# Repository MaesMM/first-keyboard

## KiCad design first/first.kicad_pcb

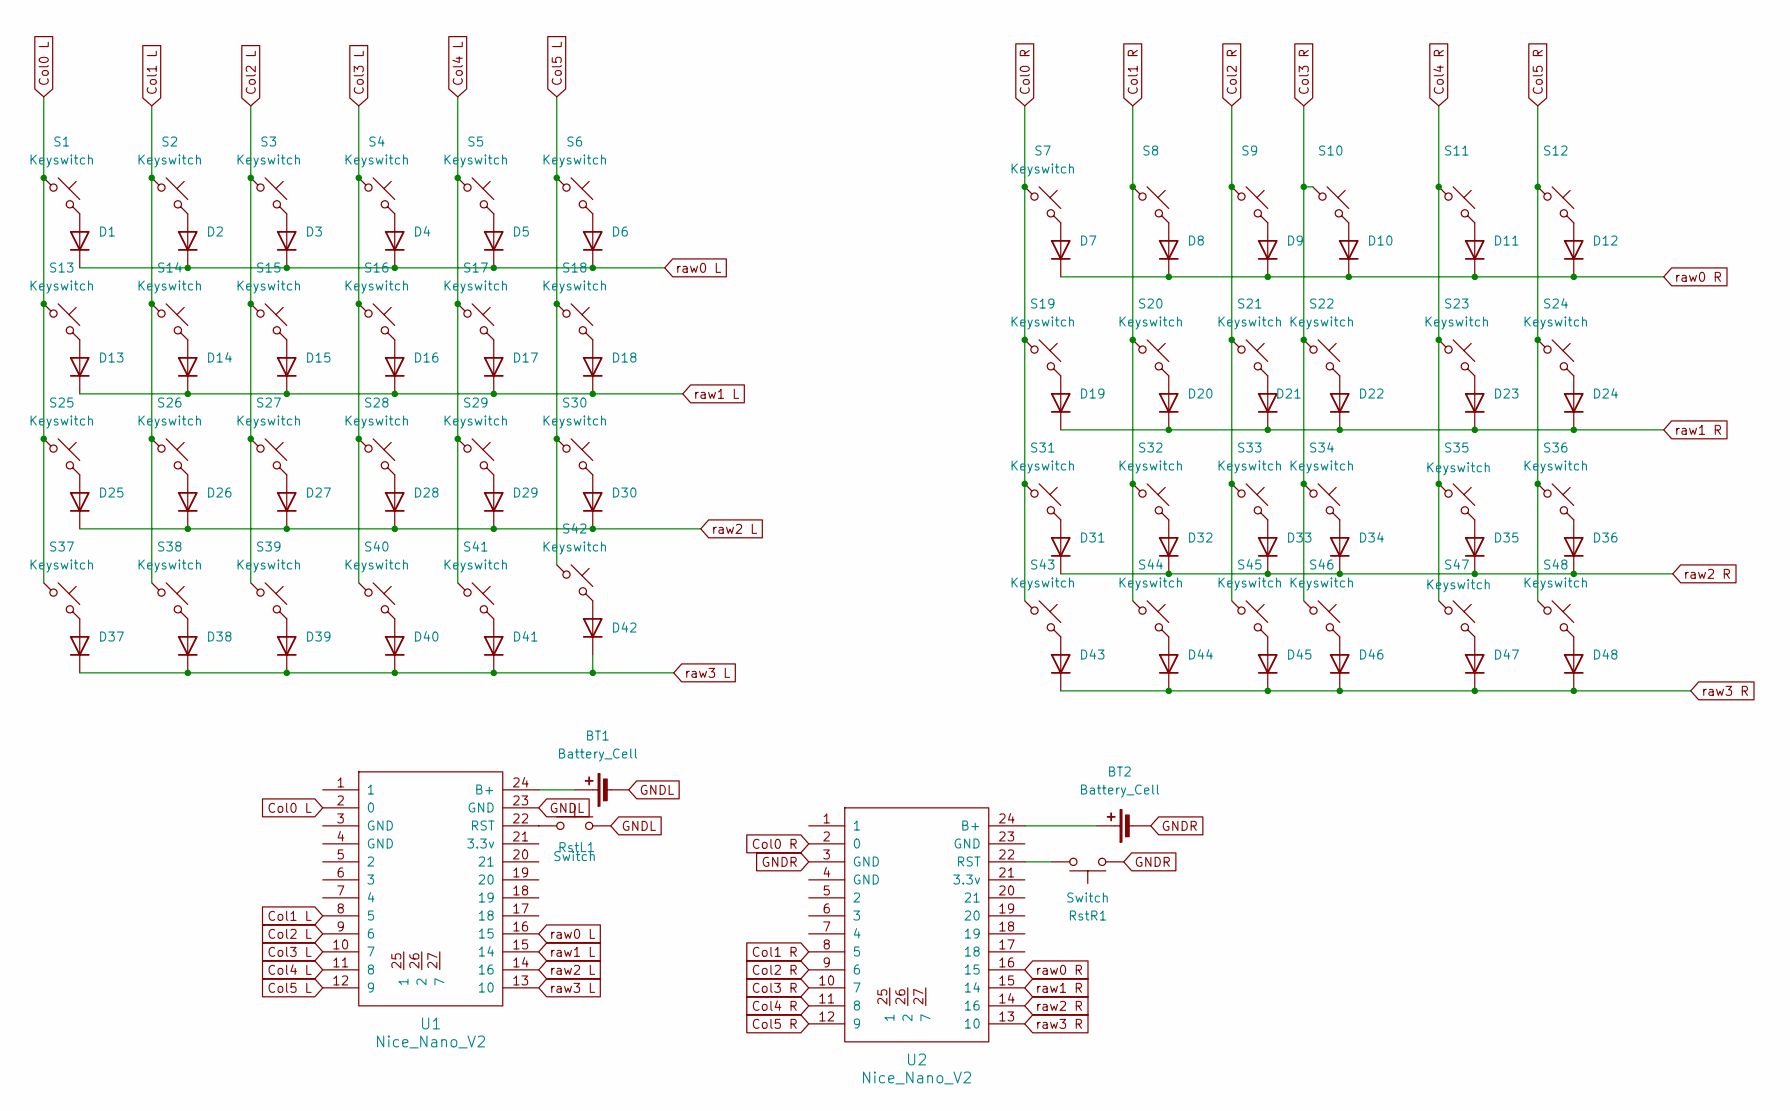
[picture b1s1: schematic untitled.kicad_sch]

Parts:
BT1, BT2: Battery_Cell; Battery
D1, D2, D3, D4, D5, D6, D7, D8, D9, D10, D11, D12, D13, D14, D15, D16, D17, D18, D19, D20, D21, D22, D23, D24, D25, D26, D27, D28, D29, D30, D31, D32, D33, D34, D35, D36, D37, D38, D39, D40, D41, D42, D43, D44, D45, D46, D47, D48: Diode; Diode_DO-35
RstL1: Switch; SW_Slide_SPDT_Straight_CK_OS102011MS2Q
RstR1: Switch; SW_Slide_SPDT_Straight_CK_OS102011MS2Q
S1, S2, S3, S4, S5, S6, S7, S8, S9, S10, S11, S12, S13, S14, S15, S16, S17, S18, S19, S20, S21, S22, S23, S24, S25, S26, S27, S28, S29, S30, S31, S32, S33, S34, S35, S36, S37, S38, S39, S40, S41, S42, S43, S44, S45, S46, S47, S48: Keyswitch; SW_Gateron_LowProfile_HotSwap_THT
U1, U2: Nice_Nano_V2

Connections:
Col0 L: S1.1, S13.1, S25.1, S37.1, U1.2 (0)
Col0 R: S7.1, S19.1, S31.1, S43.1, U2.2 (0)
Col1 L: S2.1, S14.1, S26.1, S38.1, U1.8 (5)
Col1 R: S8.1, S20.1, S32.1, S44.1, U2.8 (5)
Col2 L: S3.1, S15.1, S27.1, S39.1, U1.9 (6)
Col2 R: S9.1, S21.1, S33.1, S45.1, U2.9 (6)
Col3 L: S4.1, S16.1, S28.1, S40.1, U1.10 (7)
Col3 R: S10.1, S22.1, S34.1, S46.1, U2.10 (7)
Col4 L: S5.1, S17.1, S29.1, S41.1, U1.11 (8)
Col4 R: S11.1, S23.1, S35.1, S47.1, U2.11 (8)
Col5 L: S6.1, S18.1, S30.1, S42.1, U1.12 (9)
Col5 R: S12.1, S24.1, S36.1, S48.1, U2.12 (9)
GNDL: BT1.2 (-), RstL1.2, U1.23 (GND)
GNDR: BT2.2 (-), RstR1.1, U2.3 (GND)
unnamed: BT1.1 (+), U1.24 (B+)
unnamed: BT2.1 (+), U2.24 (B+)
unnamed: D1.2 (A), S1.2
unnamed: D2.2 (A), S2.2
unnamed: D3.2 (A), S3.2
unnamed: D4.2 (A), S4.2
unnamed: D5.2 (A), S5.2
unnamed: D6.2 (A), S6.2
unnamed: D7.2 (A), S7.2
unnamed: D8.2 (A), S8.2
unnamed: D9.2 (A), S9.2
unnamed: D10.2 (A), S10.2
unnamed: D11.2 (A), S11.2
unnamed: D12.2 (A), S12.2
unnamed: D13.2 (A), S13.2
unnamed: D14.2 (A), S14.2
unnamed: D15.2 (A), S15.2
unnamed: D16.2 (A), S16.2
unnamed: D17.2 (A), S17.2
unnamed: D18.2 (A), S18.2
unnamed: D19.2 (A), S19.2
unnamed: D20.2 (A), S20.2
unnamed: D21.2 (A), S21.2
unnamed: D22.2 (A), S22.2
unnamed: D23.2 (A), S23.2
unnamed: D24.2 (A), S24.2
unnamed: D25.2 (A), S25.2
unnamed: D26.2 (A), S26.2
unnamed: D27.2 (A), S27.2
unnamed: D28.2 (A), S28.2
unnamed: D29.2 (A), S29.2
unnamed: D30.2 (A), S30.2
unnamed: D31.2 (A), S31.2
unnamed: D32.2 (A), S32.2
unnamed: D33.2 (A), S33.2
unnamed: D34.2 (A), S34.2
unnamed: D35.2 (A), S35.2
unnamed: D36.2 (A), S36.2
unnamed: D37.2 (A), S37.2
unnamed: D38.2 (A), S38.2
unnamed: D39.2 (A), S39.2
unnamed: D40.2 (A), S40.2
unnamed: D41.2 (A), S41.2
unnamed: D42.2 (A), S42.2
unnamed: D43.2 (A), S43.2
unnamed: D44.2 (A), S44.2
unnamed: D45.2 (A), S45.2
unnamed: D46.2 (A), S46.2
unnamed: D47.2 (A), S47.2
unnamed: D48.2 (A), S48.2
unnamed: RstL1.1, U1.22 (RST)
unnamed: RstR1.2, U2.22 (RST)
raw0 L: D1.1 (K), D2.1 (K), D3.1 (K), D4.1 (K), D5.1 (K), D6.1 (K), U1.16 (15)
raw0 R: D7.1 (K), D8.1 (K), D9.1 (K), D10.1 (K), D11.1 (K), D12.1 (K), U2.16 (15)
raw1 L: D13.1 (K), D14.1 (K), D15.1 (K), D16.1 (K), D17.1 (K), D18.1 (K), U1.15 (14)
raw1 R: D19.1 (K), D20.1 (K), D21.1 (K), D22.1 (K), D23.1 (K), D24.1 (K), U2.15 (14)
raw2 L: D25.1 (K), D26.1 (K), D27.1 (K), D28.1 (K), D29.1 (K), D30.1 (K), U1.14 (16)
raw2 R: D31.1 (K), D32.1 (K), D33.1 (K), D34.1 (K), D35.1 (K), D36.1 (K), U2.14 (16)
raw3 L: D37.1 (K), D38.1 (K), D39.1 (K), D40.1 (K), D41.1 (K), D42.1 (K), U1.13 (10)
raw3 R: D43.1 (K), D44.1 (K), D45.1 (K), D46.1 (K), D47.1 (K), D48.1 (K), U2.13 (10)

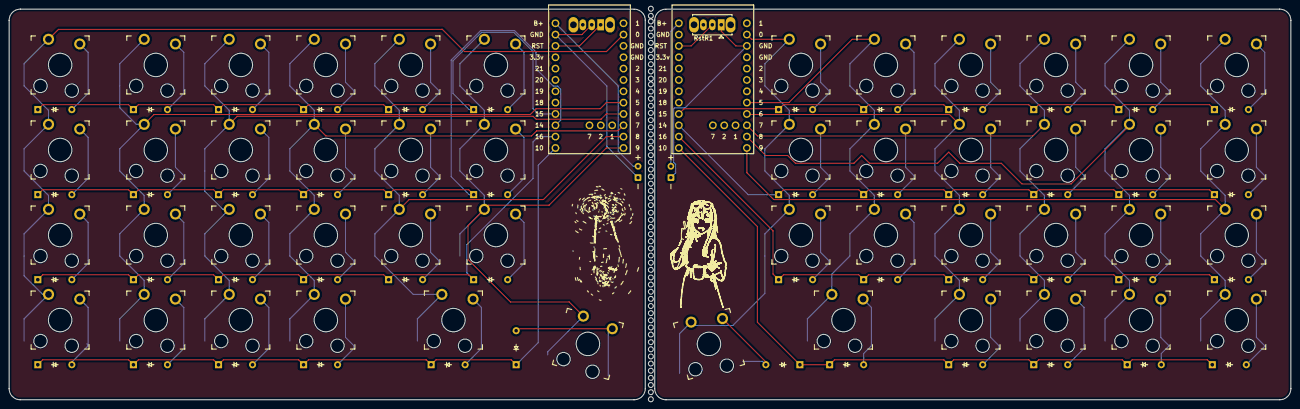
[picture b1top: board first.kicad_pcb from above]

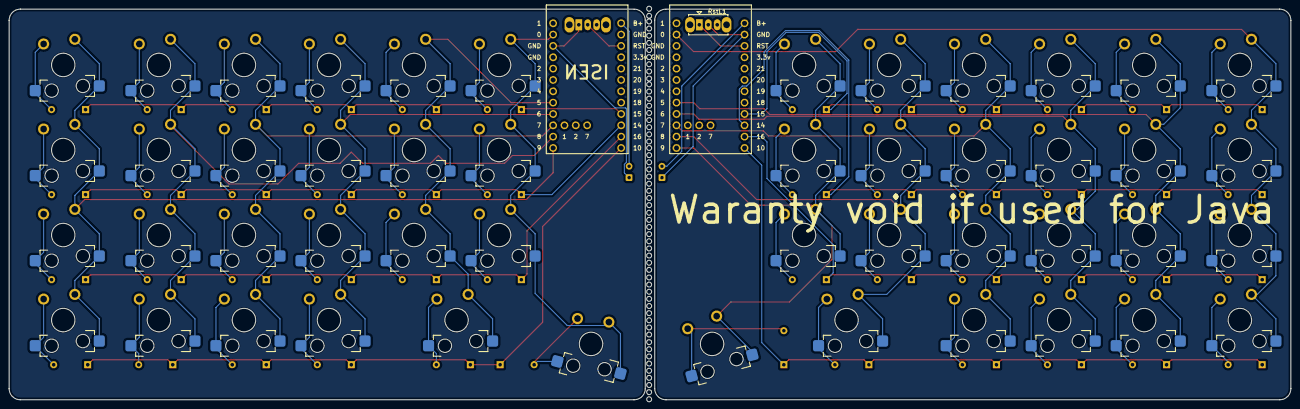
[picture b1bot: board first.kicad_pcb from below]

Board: 2 copper layers, 287.1 x 87.5 mm, 102 parts (3 on the bottom side), 74 nets.

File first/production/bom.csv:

Designator,Footprint,Quantity,Value,LCSC Part #
"_2, ",,2,,
"BT1, BT2",Battery,2,Battery_Cell,
"D1, D10, D11, D12, D13, D14, D15, D16, D17, D18, D19, D2, D20, D21, D22, D23, D24, D25, D26, D27, D28, D29, D3, D30, D31, D32, D33, D34, D35, D36, D37, D38, D39, D4, D40, D41, D42, D43, D44, D45, D46, D47, D48, D5, D6, D7, D8, D9",Diode_DO-35,48,Diode,
"RSTL1, RSTR1",SW_Slide_SPDT_Straight_CK_OS102011MS2Q,2,Switch,
"S1, S10, S11, S12, S13, S14, S15, S16, S17, S18, S19, S2, S20, S21, S22, S23, S24, S25, S26, S27, S28, S29, S3, S30, S31, S32, S33, S34, S35, S36, S37, S38, S39, S4, S40, S41, S42, S43, S44, S45, S46, S47, S48, S5, S6, S7, S8, S9",SW_Gateron_LowProfile_HotSwap_THT,48,Keyswitch,
"U1, U2",Nice_Nano_V2,2,Nice_Nano_V2,

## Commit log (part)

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2025-09-19 pcb files
2025-11-29 feat:initial firmware
